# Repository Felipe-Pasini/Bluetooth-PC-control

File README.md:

# Bluetooth-PC-Control

Application of a computer remote control, using bluetooth communication.
The microcontroller used was a STM32F103C8T6 (also known as BluePill) and the bluetooth communication was made using a HC-05 module.

For the PC to recognize the control, a C application (.exe) file was developed, which creates a virtual keyboard/mouse and uses the data received by the serial port (bluetooth) as it's input. The application must be run in background while the control is in operation.

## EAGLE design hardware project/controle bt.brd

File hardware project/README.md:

The hardware was developed using Eagle 7.6. 
Here are available also the libraries needed to for the HC-05 module, the BluePill board and also the joystick, which is from an Arduino kit.

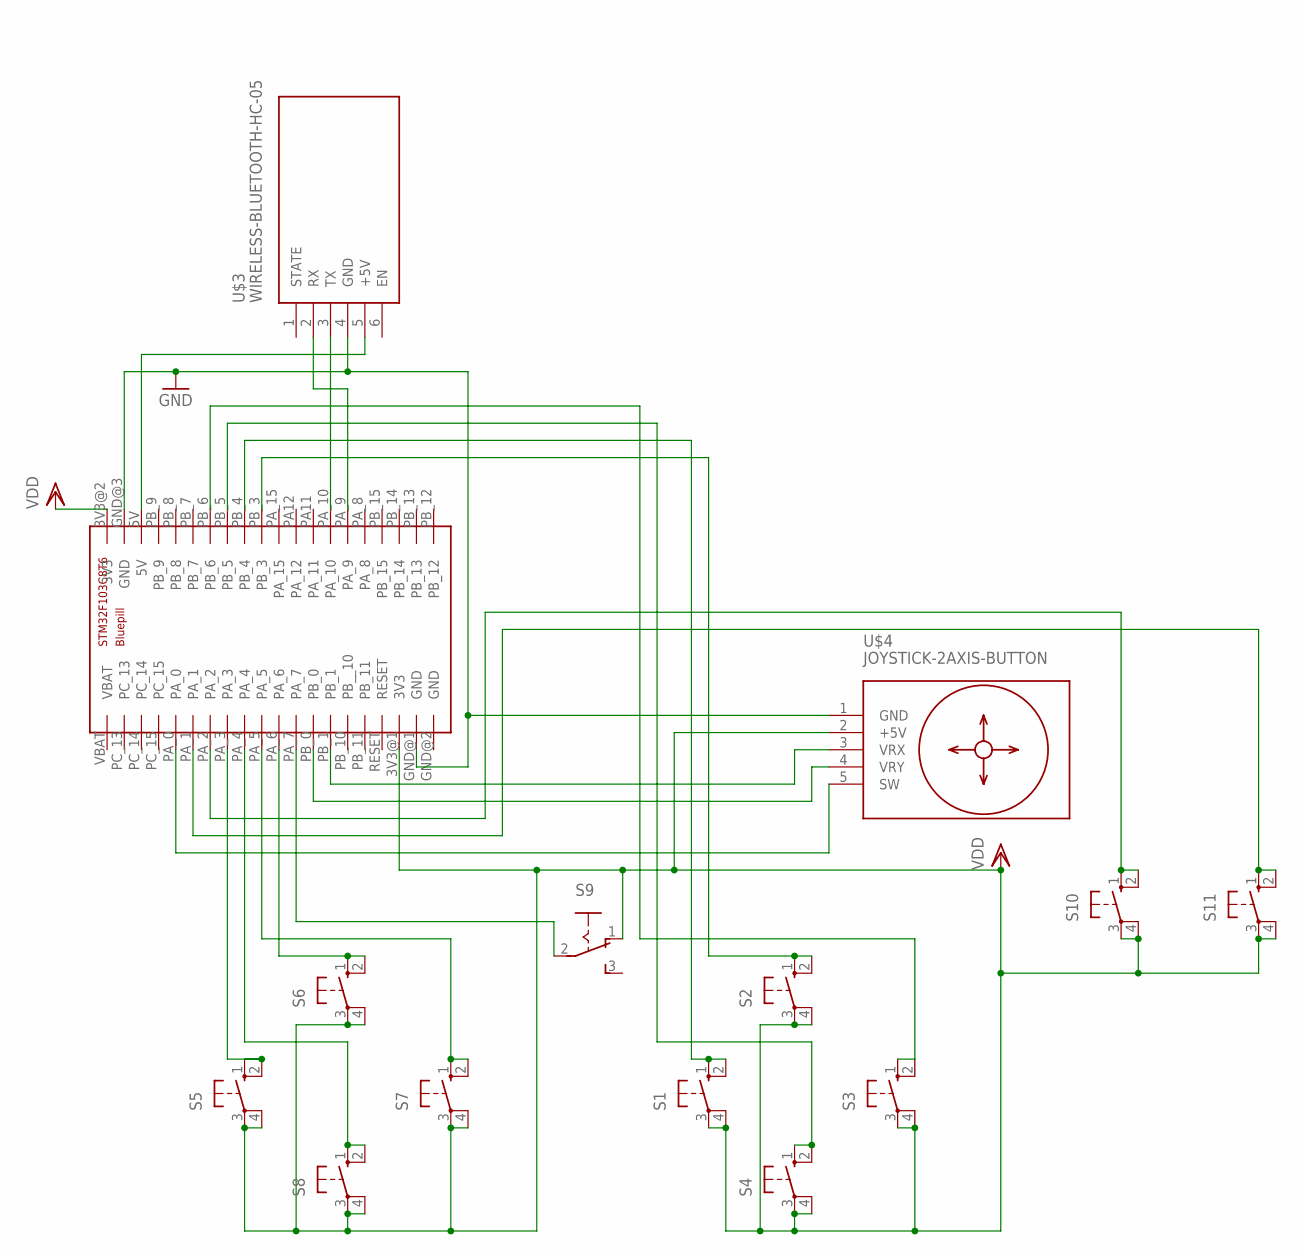
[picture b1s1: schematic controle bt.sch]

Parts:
S1, S2, S3, S4, S5, S6, S7, S8, S10, S11: 10-XX; B3F-10XX
S9: 255SB
U$2: STM32_BLUEPILL
U$3: WIRELESS-BLUETOOTH-HC-05
U$4: JOYSTICK-2AXIS-BUTTON

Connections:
GND: U$2.GND@1 (GND), U$2.GND@3 (GND), U$3.4 (GND), U$4.1 (GND)
unnamed: S10.1 (S), S10.2 (S1), U$2.PA_2
unnamed: U$2.PA_10, U$3.3 (TX)
unnamed: U$2.PA_9, U$3.2 (RX)
unnamed: S11.1 (S), S11.2 (S1), U$2.PA_1
unnamed: U$2.5V, U$3.5 (+5V)
unnamed: U$2.PA_0, U$4.5 (SW)
unnamed: U$2.PB_1, U$4.3 (VRX)
unnamed: U$2.PB_0, U$4.4 (VRY)
unnamed: S8.1 (S), S8.2 (S1), U$2.PA_4
unnamed: S5.1 (S), S5.2 (S1), U$2.PA_3
unnamed: S6.1 (S), S6.2 (S1), U$2.PA_6
unnamed: S1.1 (S), S1.2 (S1), U$2.PB_4
unnamed: S4.1 (S), S4.2 (S1), U$2.PB_5
unnamed: S7.1 (S), S7.2 (S1), U$2.PA_5
unnamed: S2.1 (S), S2.2 (S1), U$2.PB_3
unnamed: S9.2, U$2.PA_7
unnamed: S3.1 (S), S3.2 (S1), U$2.PB_6
VDD: S1.3, S1.4 (P1), S2.3, S2.4 (P1), S3.3, S3.4 (P1), S4.3, S4.4 (P1), S5.3, S5.4 (P1), S6.3, S6.4 (P1), S7.3, S7.4 (P1), S8.3, S8.4 (P1), S9.1 (O), S10.3, S10.4 (P1), S11.3, S11.4 (P1), U$2.3V3@1 (3V3), U$2.3V3@2 (3V3), U$4.2 (+5V)

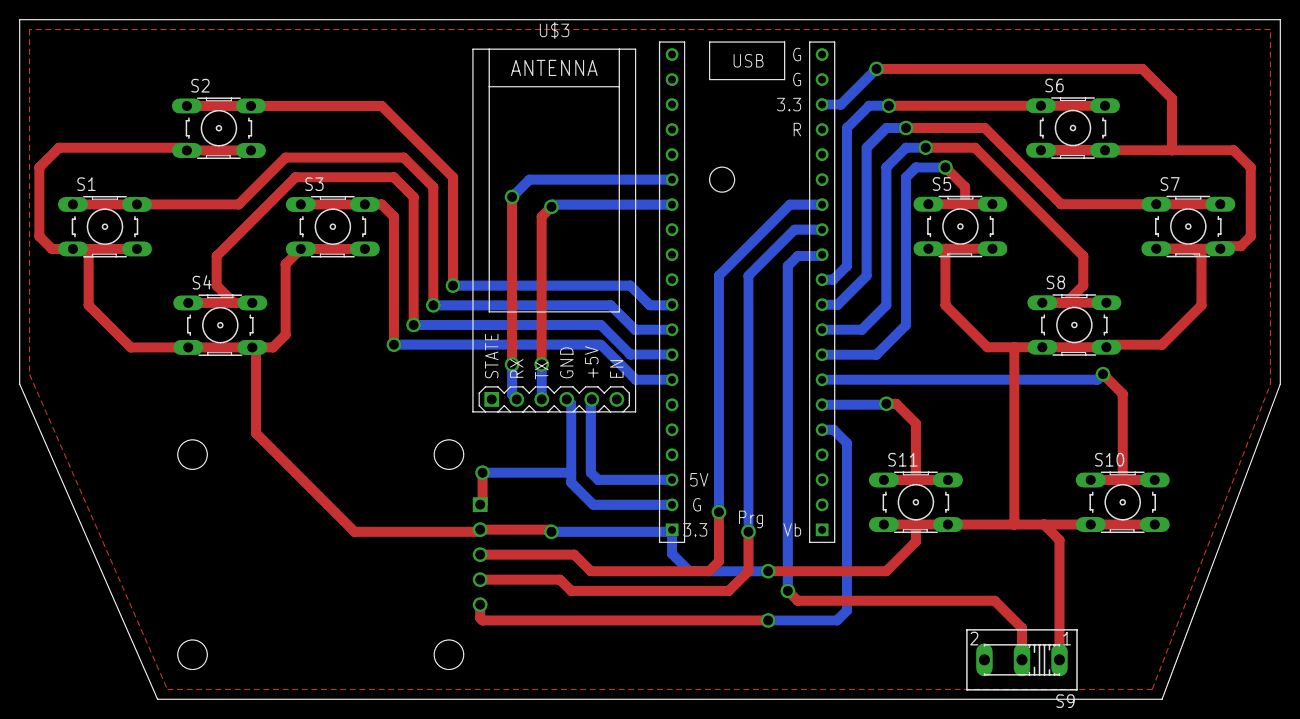
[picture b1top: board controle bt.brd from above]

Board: 2 copper layers, 128.0 x 69.0 mm, 14 parts (1 on the bottom side), 19 nets.

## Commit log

2022-10-19 Create Eagle
2022-10-19 Create mciro
2022-10-19 Create code blocks
2022-10-19 Rename mciro to Micro.md

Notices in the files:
parts and their libraries:
diy-modules: Released under the Creative Commons Attribution 4.0 International License: http://creativecommons.org/licenses/by/4.0
